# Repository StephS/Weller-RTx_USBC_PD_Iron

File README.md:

# Weller-RTx_USBC_PD_Iron
USB Type C Soldering Iron<br />
Utilizes the ST Micro STM32G431 controller with USB Type C Power delivery support<br />
Interactive BOM: https://stephs.github.io/Weller-RTx_USBC_PD_Iron/index.html

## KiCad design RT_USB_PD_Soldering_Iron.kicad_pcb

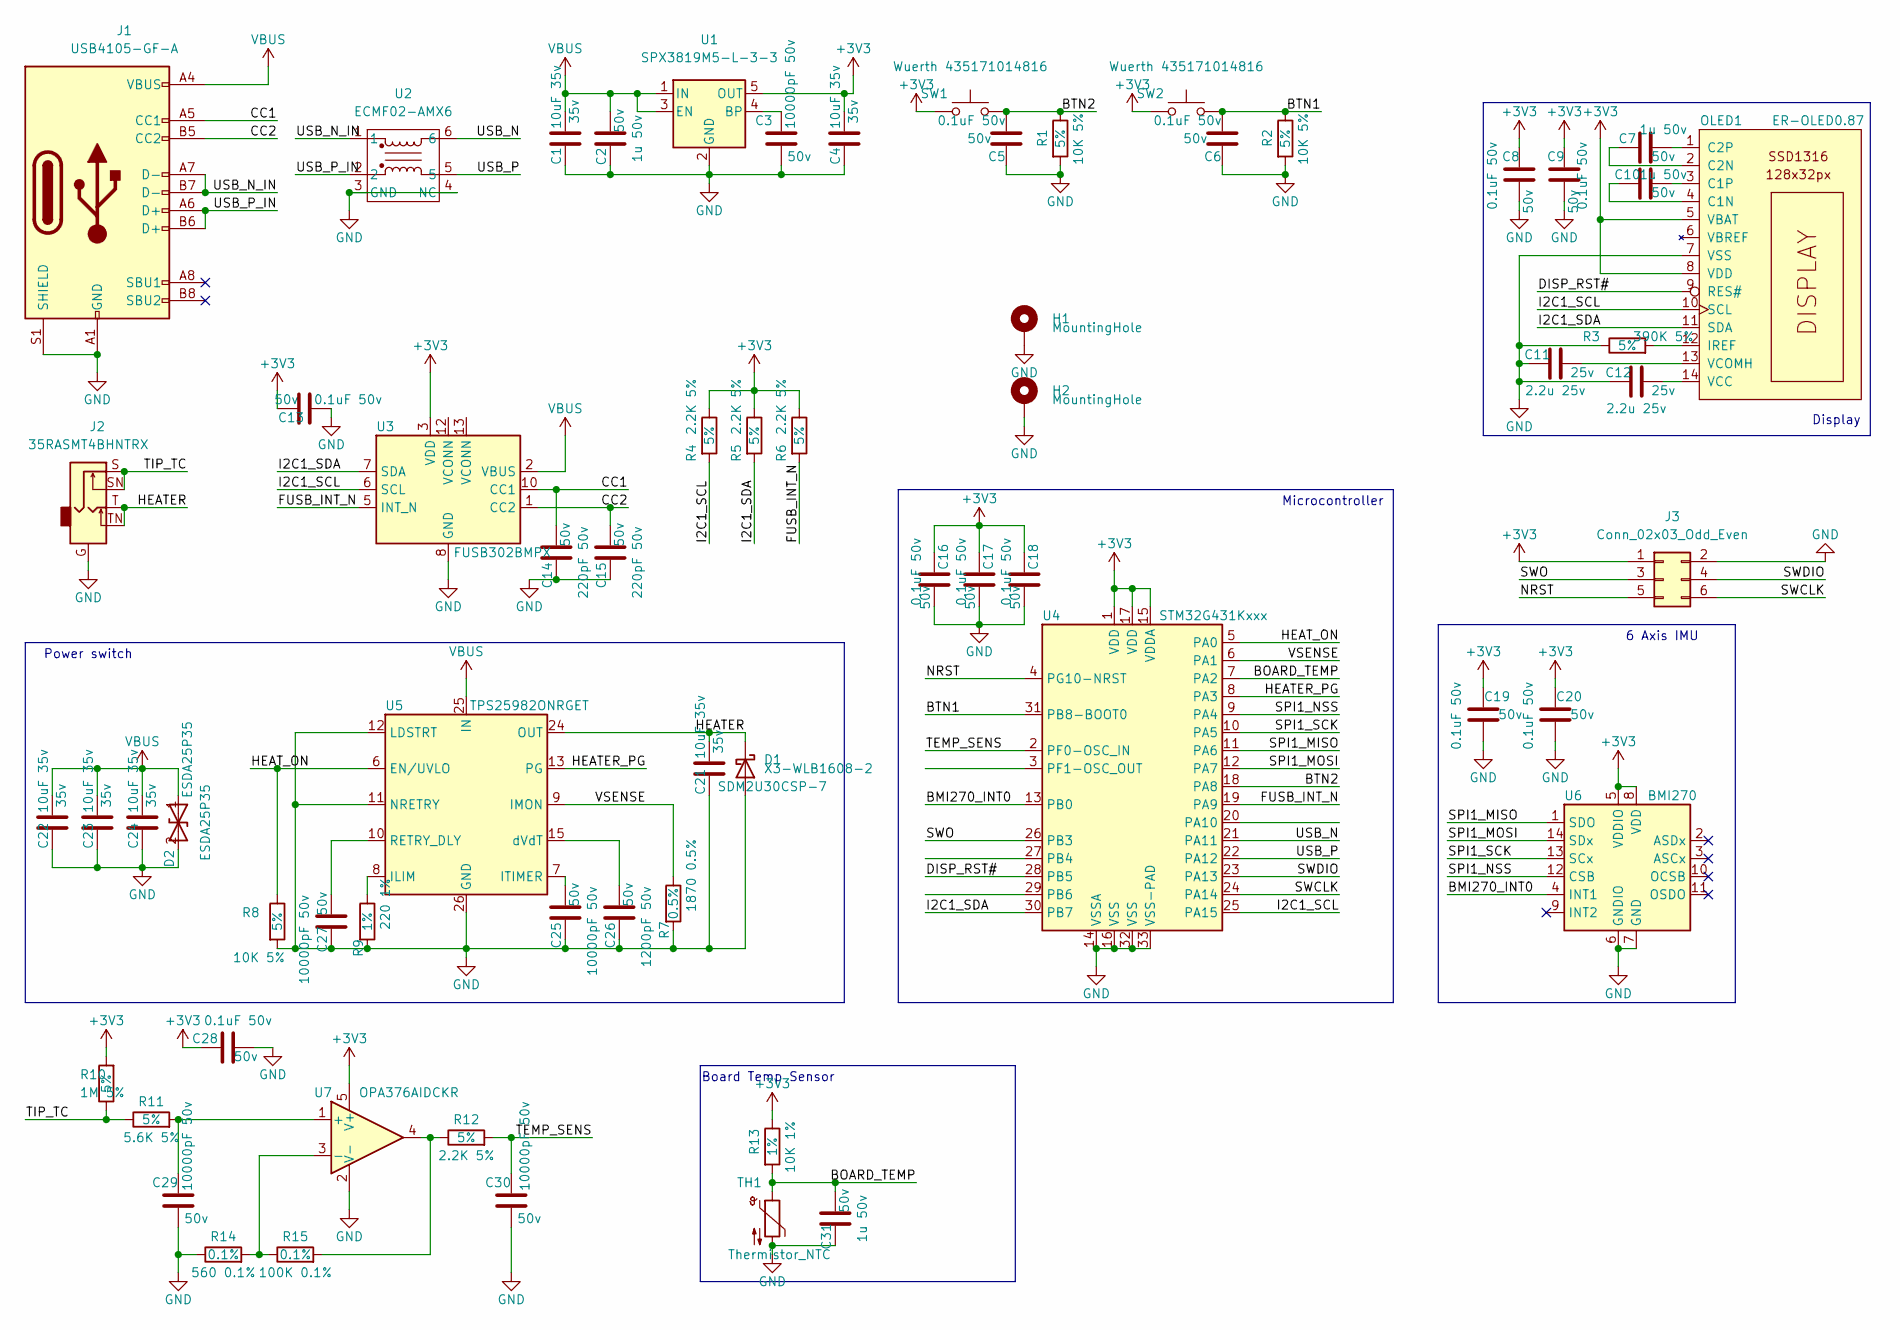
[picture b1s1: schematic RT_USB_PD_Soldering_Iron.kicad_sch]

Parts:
C1, C4, C21, C22, C23, C24: 10uF 35v; C_0603_1608Metric_Pad1.05x0.95mm_HandSolder; Voltage 35v
C2, C7, C10, C31: 1u 50v; C_0402_1005Metric; Voltage 50v
C3, C25, C27, C29, C30: 10000pF 50v; C_0402_1005Metric; Voltage 50v
C5, C6, C8, C9, C13, C16, C17, C18, C19, C20, C28: 0.1uF 50v; C_0402_1005Metric; Voltage 50v
C11, C12: 2.2u 25v; C_0402_1005Metric; Voltage 25v
C14, C15: 220pF 50v; C_0402_1005Metric; Voltage 50v
C26: 1200pF 50v; C_0402_1005Metric; Voltage 50v
D1: X3-WLB1608-2; Part SDM2U30CSP-7
D2: ESDA25P35; D_1610; Part ESDA25P35
H1, H2: MountingHole; MountingHole_2.2mm_M2_ISO7380_Pad
J1: USB4105-GF-A; GCT_USB4105
J2: 35RASMT4BHNTRX; Jack_3.5mm_CUI_SJ-3524-SMT_Horizontal_cutout
J3: Conn_02x03_Odd_Even; PinHeader_2x03_P1.00mm_Vertical_SMD
OLED1: ER-OLED0.87
R1, R2, R8: 10K 5%; R_0402_1005Metric; Tolerance 5%
R3: 390K 5%; R_0402_1005Metric; Tolerance 5%
R4, R5, R6, R12: 2.2K 5%; R_0402_1005Metric; Tolerance 5%
R7: 1870 0.5%; R_0402_1005Metric; Tolerance 0.5%
R9: 220 1%; R_0402_1005Metric; Tolerance 1%
R10: 1M 5%; R_0402_1005Metric; Tolerance 5%
R11: 5.6K 5%; R_0402_1005Metric; Tolerance 5%
R13: 10K 1%; R_0402_1005Metric; Tolerance 1%
R14: 560 0.1%; R_0402_1005Metric; Tolerance 0.1%
R15: 100K 0.1%; R_0402_1005Metric; Tolerance 0.1%
SW1, SW2: Wuerth 435171014816; SW_Push_1P1T_NO_Vertical_Wuerth_434133025816; Part Wuerth 435171014816
TH1: Thermistor_NTC; R_0402_1005Metric
U1: SPX3819M5-L-3-3; SOT-23-5
U2: ECMF02-AMX6; ST_UQFN-6L_1.5x1.7mm_Pitch0.5mm
U3: FUSB302BMPX; WQFN-14-1EP_2.5x2.5mm_P0.5mm_EP1.45x1.45mm
U4: STM32G431Kxxx; QFN-32-1EP_5x5mm_P0.5mm_EP3.45x3.45mm
U5: TPS25982ONRGET; VQFN-24-1EP_4x4mm_P0.5mm_EP2.45x2.45mm
U6: BMI270; Bosch_LGA-14_3x2.5mm_P0.5mm
U7: OPA376AIDCKR; SOT-353_SC-70-5

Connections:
+3V3: C4.1, C8.1, C9.1, C13.2, C16.1, C17.1, C18.1, C19.1, C20.1, C28.1, J3.1, OLED1.5 (VBAT), OLED1.8 (VDD), R4.1, R5.1, R6.1, R10.2, R13.1, SW1.1, SW2.1, U1.5 (OUT), U3.3 (VDD), U3.4 (VDD), U4.1 (VDD), U4.15 (VDDA), U4.17 (VDD), U6.5 (VDDIO), U6.8 (VDD), U7.5 (V+)
/BMI270_INT0: U4.13 (PB0), U6.4 (INT1)
/BOARD_TEMP: C31.2, R13.2, TH1.1, U4.7 (PA2)
/BTN1: C6.2, R2.1, SW2.2, U4.31 (PB8-BOOT0)
/BTN2: C5.2, R1.1, SW1.2, U4.18 (PA8)
/CC1: C14.2, J1.A5 (CC1), U3.10 (CC1), U3.11 (CC1)
/CC2: C15.2, J1.B5 (CC2), U3.1 (CC2), U3.14 (CC2)
/DISP_RST#: OLED1.9 (RES#), U4.28 (PB5)
/FUSB_INT_N: R6.2, U3.5 (INT_N), U4.19 (PA9)
/HEATER: C21.1, D1.1 (K), J2.T, J2.TN, U5.17 (OUT), U5.18 (OUT), U5.19 (OUT), U5.20 (OUT), U5.21 (OUT), U5.22 (OUT), U5.23 (OUT), U5.24 (OUT)
/HEATER_PG: U4.8 (PA3), U5.13 (PG)
/HEAT_ON: R8.1, U4.5 (PA0), U5.6 (EN/UVLO)
/I2C1_SCL: OLED1.10 (SCL), R4.2, U3.6 (SCL), U4.25 (PA15)
/I2C1_SDA: OLED1.11 (SDA), R5.2, U3.7 (SDA), U4.30 (PB7)
/NRST: J3.5, U4.4 (PG10-NRST)
/SPI1_MISO: U4.11 (PA6), U6.1 (SDO)
/SPI1_MOSI: U4.12 (PA7), U6.14 (SDx)
/SPI1_NSS: U4.9 (PA4), U6.12 (CSB)
/SPI1_SCK: U4.10 (PA5), U6.13 (SCx)
/SWCLK: J3.6, U4.24 (PA14)
/SWDIO: J3.4, U4.23 (PA13)
/SWO: J3.3, U4.26 (PB3)
/TEMP_SENS: C30.1, R12.2, U4.2 (PF0-OSC_IN)
/TIP_TC: J2.S, J2.SN, R10.1, R11.1
/USB_N: U2.6, U4.21 (PA11)
/USB_N_IN: J1.A7 (D-), J1.B7 (D-), U2.1
/USB_P: U2.5, U4.22 (PA12)
/USB_P_IN: J1.A6 (D+), J1.B6 (D+), U2.2
/VSENSE: R7.1, U4.6 (PA1), U5.9 (IMON)
GND: C1.2, C2.1, C3.2, C4.2, C5.1, C6.1, C8.2, C9.2, C11.1, C12.1, C13.1, C14.1, C15.1, C16.2, C17.2, C18.2, C19.2, C20.2, C21.2, C22.2, C23.2, C24.2, C25.1, C26.1, C27.1, C28.2, C29.2, C30.2, C31.1, D1.2 (A), D2.2 (A2), H1.1, H2.1, J1.A1 (GND), J1.A12 (GND), J1.B1 (GND), J1.B12 (GND), J1.S1 (SHIELD), J2.G, J3.2, OLED1.7 (VSS), R1.2, R2.2, R3.1, R7.2, R8.2, R9.2, R14.1, TH1.2, U1.2 (GND), U2.3 (GND), U2.4 (NC), U3.8 (GND), U3.9 (GND), U3.15 (GND), U4.14 (VSSA), U4.16 (VSS), U4.32 (VSS), U4.33 (VSS-PAD), U5.4 (GND), U5.5 (GND), U5.11 (NRETRY), U5.12 (LDSTRT), U5.14 (GND), U5.26 (GND), U6.6 (GNDIO), U6.7 (GND), U7.2 (V-)
IN: C1.1, C2.2, C22.1, C23.1, C24.1, D2.1 (A1), J1.A4 (VBUS), J1.A9 (VBUS), J1.B4 (VBUS), J1.B9 (VBUS), U1.1 (IN), U1.3 (EN), U3.2 (VBUS), U5.1 (IN), U5.2 (IN), U5.3 (IN), U5.16 (IN), U5.25 (IN)
unnamed: C3.1, U1.4 (BP)
unnamed: C7.1, OLED1.2 (C2N)
unnamed: C7.2, OLED1.1 (C2P)
unnamed: C10.1, OLED1.4 (C1N)
unnamed: C10.2, OLED1.3 (C1P)
unnamed: C11.2, OLED1.13 (VCOMH)
unnamed: C12.2, OLED1.14 (VCC)
unnamed: C25.2, U5.7 (ITIMER)
unnamed: C26.2, U5.15 (dVdT)
unnamed: C27.2, U5.10 (RETRY_DLY)
unnamed: C29.1, R11.2, U7.1 (+)
unnamed: OLED1.12 (IREF), R3.2
unnamed: R9.1, U5.8 (ILIM)
unnamed: R12.1, R15.2, U7.4
unnamed: R14.2, R15.1, U7.3 (-)

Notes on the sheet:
Power switch
Board Temp Sensor
Microcontroller
6 Axis IMU
Display

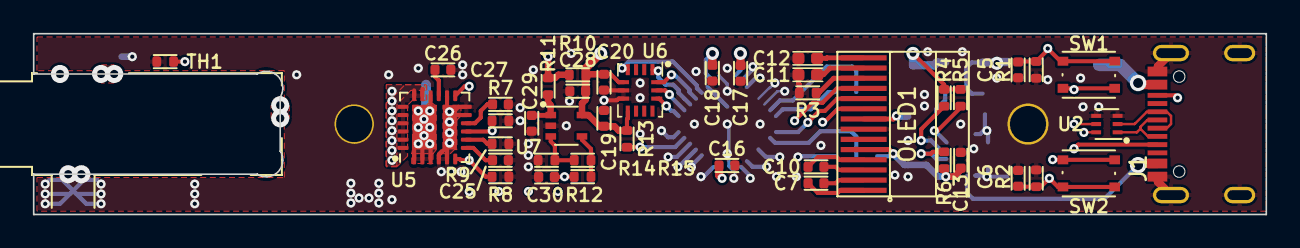
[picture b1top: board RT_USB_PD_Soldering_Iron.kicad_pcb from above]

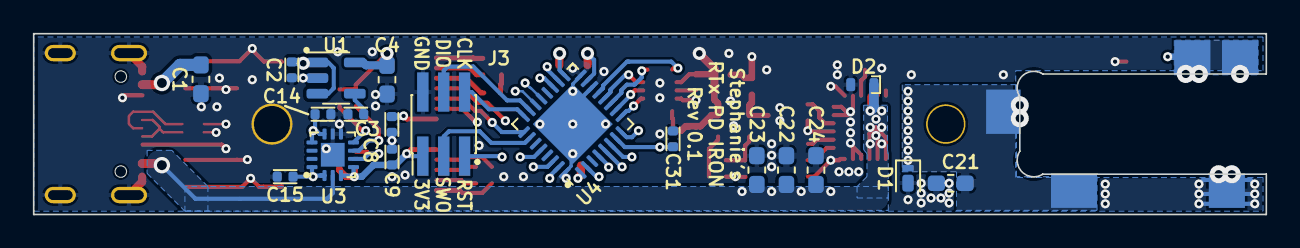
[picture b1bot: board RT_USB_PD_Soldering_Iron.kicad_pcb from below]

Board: 4 copper layers, 75.0 x 11.0 mm, 64 parts (19 on the bottom side), 46 nets.

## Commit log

2020-09-21 First revision
    First revision, to be reviewed
2020-09-21 Add Schematic
    Add Schematic and minor layout changes
2020-09-21 Adjust for oled cable
    added some room for the oled bend radius.
2020-09-21 Move C12 Silk
2020-09-24 New board layout
    New layout. Nothing is around the USB connector now. 1mm keepout around the entire board edge. I actually like this layout!
2020-09-24 Fix button position
    one button was off by 0.5mm LED position was off too...
2020-09-24 Do i want to save this backups? maybe...
    these backups were of various layouts.
2020-09-24 Update silkscreen
    Update silkscreen, minor layour changes
2020-09-30 Update Headphone connector footprint
    updating the footprint based on actual measurements.
2020-09-30 widen cut for microphone jack
    widen the cut by 0.1mm
2020-09-30 Improve XTAL circuit
    reduce the length of the xtal traces, move capacitors, and ensure GND encapsulation.
    Via diameter has been reduced to .605 from .7
2020-09-30 Update Silkscreen
2020-09-30 Update Clearance
2020-10-01 Remove backups
2020-10-01 Add updated board
    Length set to 90mm!
2020-10-01 Update Gerbers
2020-10-01 New Images
2020-10-02 Update readme with images if board
2020-10-03 Removed LED and reduced size to 80mm
    Shortest!
2020-10-03 add fpc connector
    it's slightly smaller, so maybe good?
2020-10-04 Reduce board to 75mm length
    Knocked off another 5mm
    modified USB connector pads. Increased connector board edge to meet 1mm overhang.
    Replaced a few components with new ones (smaller, lower cost).
    VReg, Usb ESD protection, and Op-AMP.
2020-10-04 change analog pins for improved routing
2020-10-05 Update silkscreen and gerbers
    moved parts a tiny bit for easier hand soldering.
2020-10-06 Move buttons away from USB connector
    Was able to move the OLED display by 0.5mm and moved the buttons 0.5mm further from the connector.
2020-10-06 Adjust Silk and run DRC
2020-10-10 Update to latest nightly
    Application: KiCad
    Version: (5.99.0-3809-g61f1f7d948), release build
    Libraries:
    wxWidgets 3.0.5
    libcurl/7.71.0 OpenSSL/1.1.1g (Schannel) zlib/1.2.11 brotli/1.0.7 libidn2/2.3.0 libpsl/0.21.0 (+libidn2/2.3.0) libssh2/1.9.0 nghttp2/1.41.0
    Platform: Windows 8 (build 9200), 64-bit edition, 64 bit, Little endian, wxMSW
2020-10-18 update libs/parts
    update 0402 footprints for silkscreen
    move volate/tolerance to value
2020-10-19 Minor changes
    moved oled connector slightly. Moved I2C pullup resistors
2020-10-20 minor layout changes
2020-10-20 redo USB traces with impedence calculations
    rename usb traces and do calculations for 90 ohm impedence
    also change voltage sense resistors to higher values
2020-10-20 complete ground path for usb
2020-10-20 more usb improvements
2020-10-20 minor trace changes
2020-10-21 Add castellated holes, improve connector cutout and pad placement
    castellated holes to hopefully increase mechanical stability.
    cut into corners
    update schematic PDF.
2020-10-22 Update USB connector
    move the pads 0.2mm for better wetting.
    increase the drill holes for more adjustment.
2020-10-22 Create PinHeader_2x03_P1.27mm_Vertical_SMD.kicad_mod
    Add a 2x3 1.27mm pin header
2020-10-22 remove test points and replace with connector. fix USB nets
    also adjust default thermals for zone, sync pcb with schematic
2020-10-22 remove old DRC exclusions
2020-10-22 Update gerbers for release. 75mm_V2 sent to OshPark
2020-10-22 Update buttons to use active-high
    by using active high, button1 allows boot mode selection when pressed.
2020-10-22 update gerbers to v3
2020-10-23 Group all used footprints in a local library
2020-10-24 Update Power voltage circuit to higher precision and lower cost components
    change to 12K + 75K 0.5%
2020-10-29 update thermals for high side switch
    or more accurately, add thermals. Previously difficult to hand solder. Hopefully this helps.
2020-10-29 Create C_0402_1005Metric_Pad0.74x0.62mm_HandSolder.kicad_mod
    Add new footprint for slightly larger capacitors, based on HandSolder
2020-10-29 Update footprints for R26, R27
    These 2.2uF capacitors are slightly larger than normal. Requires bigger pads.
2020-10-30 Modify CC lines
    Add capacitors to CC lines. Tie in DBCC to the CC lines.
2020-10-30 New gerbers and schematics
    To be built
2020-10-30 slight change in capacitor layout
2021-04-02 First revision 0.1
    Rev 0.1 untested unverified.
2021-04-02 Add mounting holes, change diode
    added mounting holes and changed the diode to a much smaller part.
2021-04-03 Power trace changes, pin changes
    updated the power traces for better current return path. Connected PG from the high side switch.
    Lots of pin changes for better layout.
    re-annotated schematic
2021-04-03 Update VQFN24 Footprint
    update the footprint for slightly elongated pads.
2021-04-03 Housekeeping
    cleanup. Moved R6. Update USB4105 connector (elongate holes slightly)
2021-04-03 Update OLED keepout, 3D models
    increase the keepout slightly.
    add more 3D models
    fix error in USB4105 layout
2021-04-03 Change mounting holes to Plated Through Holes
2021-04-03 V0.1 Gerbers
2021-04-03 Final tweaks before sending to Fab, fix diode D2 orientation
2021-04-04 Add OLED 3D Model
    OLED 3D Model added
2021-04-21 Add BOM. Update to nightly.
2021-04-22 Create index.html
    Testing docs
2021-04-22 Set theme jekyll-theme-midnight
2021-04-22 move BOM
2021-04-23 Set bom to Index.
2021-04-23 Set theme jekyll-theme-hacker
2021-04-23 Update part values to part #
    Update SW1, SW2, D1, D2 values to the part numbers
